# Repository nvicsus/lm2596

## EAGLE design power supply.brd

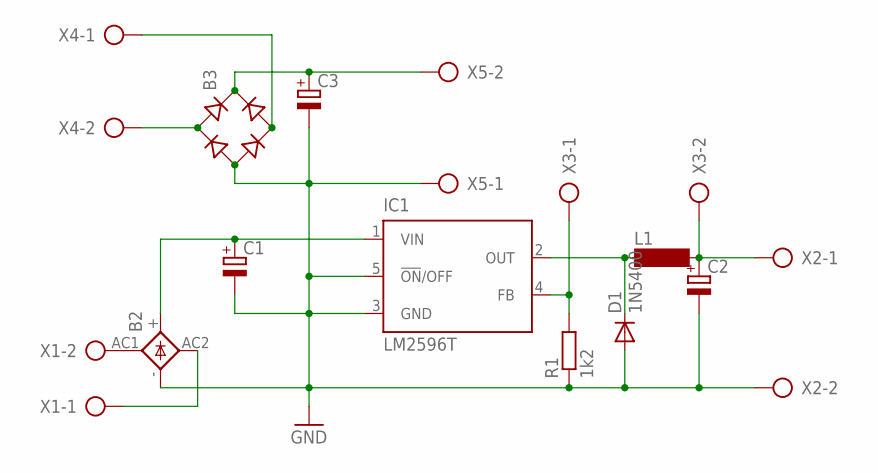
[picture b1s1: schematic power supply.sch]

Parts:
B2: FB15
B3: B-DIL
C1, C2, C3: CPOL-EUTT5D11; TT5D11
D1: 1N5400; DO201-15
IC1: LM2596T; T05D
L1: SD12K-82
R1: 1k2; 0207/10
X1, X2, X3, X4, X5: AK300/2

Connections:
+12V: B2.+, C1.+, IC1.1 (VIN)
GND: B2.-, B3.-, C1.-, C2.-, C3.-, D1.A, IC1.3 (GND), IC1.5 (!ON!/OFF), R1.1, X2.2, X5.1
unnamed: IC1.4 (FB), R1.2, X3.1
unnamed: B2.AC2, X1.1
unnamed: C2.+, L1.2, X2.1, X3.2
unnamed: B2.AC1, X1.2
unnamed: B3.AC1, X4.2
unnamed: D1.C, IC1.2 (OUT), L1.1
unnamed: B3.AC2, X4.1
unnamed: B3.+, C3.+, X5.2

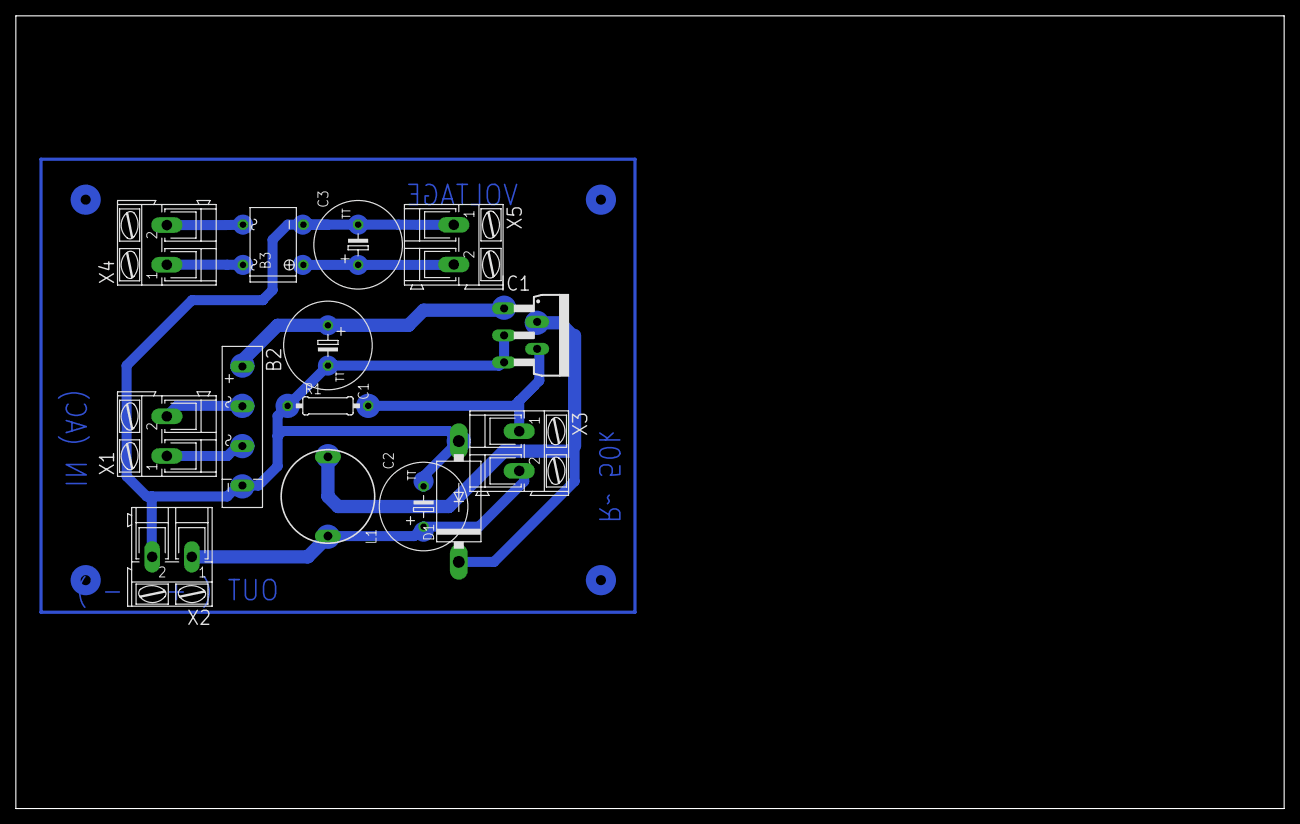
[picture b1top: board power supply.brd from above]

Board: 2 copper layers, 160.0 x 100.0 mm, 14 parts (0 on the bottom side), 10 nets.

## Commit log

2015-04-16 pure lm2596

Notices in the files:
parts and their libraries:
SparkFun: Licensing: CC v3.0 Share-Alike You are welcome to use this library for commercial purposes.
